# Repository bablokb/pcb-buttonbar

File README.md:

Project pcb-buttonbar
=====================

Overview
--------

This project contains the KiCAD files for a button-bar with
six buttons. Each button uses some additional hardware-components to
debounce the button:

The buttons are pulled up using R1. R2 and C1 serve as a lowpass-filter,
i.e. high frequency bouncing is filtered out. The final inverter, a
74HC14 is a Schmitt-Trigger type inverter. This inverter switches from
high to low at a different level than from low to high (hysteresis),
so this will convert the curve from the RC-filter to sharp edge.

Goodies
-------

The buttonbar supports buttons with four pins spaced 5.08mm x 5.08mm.
Note that normal buttons have spacings of 6.5mm x 4.5mm. 
In addition to the debounce-logic (bottom side of the pcb), there are optional
LEDs on the top.

The footprints for the top-side are 1206, suitable for hand-soldering.
The bottom-side uses 0603, ideal for automatic assembly.

Production Files
----------------

In the directory `production_files` you will find gerber-files, bom and cpl-file
suitable for JCLPCB. Migrating to a format suitable for your favorite
pcb-assembly service should be straightforward.

Test Program
------------

The directory `src` contains a simple test program. Without the debouncing
in hardware, you would have to pass an additional parameter to the
Button-constructor for debouncing in software.

License
-------

Shield: [![CC BY-SA 4.0][cc-by-sa-shield]][cc-by-sa]

This work is licensed under a
[Creative Commons Attribution-ShareAlike 4.0 International
License][cc-by-sa].

[![CC BY-SA 4.0][cc-by-sa-image]][cc-by-sa]

[cc-by-sa]: http://creativecommons.org/licenses/by-sa/4.0/
[cc-by-sa-image]: https://licensebuttons.net/l/by-sa/4.0/88x31.png
[cc-by-sa-shield]:
https://img.shields.io/badge/License-CC%20BY--SA%204.0-lightgrey.svg

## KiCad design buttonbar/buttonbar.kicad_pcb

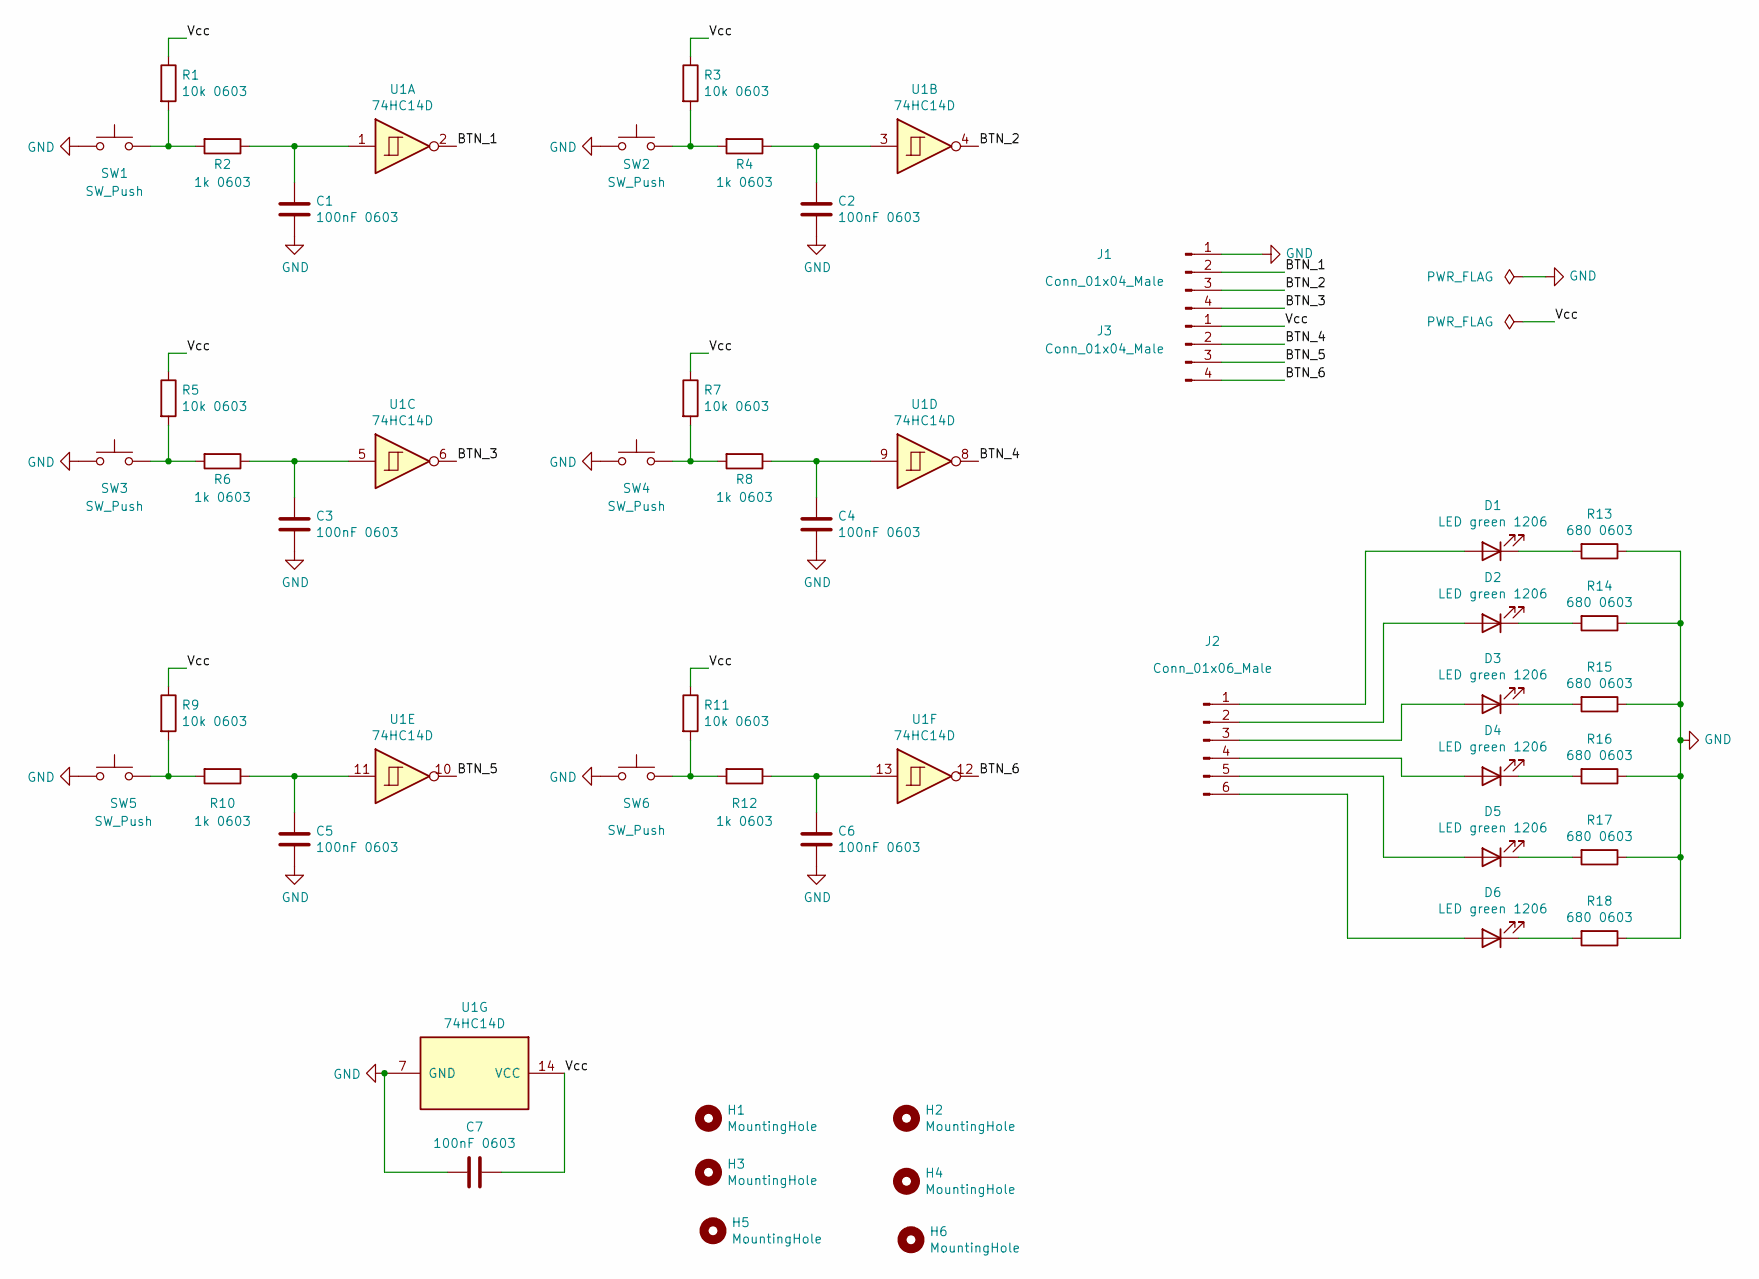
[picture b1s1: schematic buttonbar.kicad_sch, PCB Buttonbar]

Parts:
C1, C2, C3, C4, C5, C6, C7: 100nF 0603; C_0603_1608Metric; LCSC C14663
D1, D2, D3, D4, D5, D6: LED green 1206; LED_1206_3216Metric_Pad1.42x1.75mm_HandSolder
H1, H2, H3, H4, H5, H6: MountingHole; MountingHole_2.5mm
J1, J3: Conn_01x04_Male; PinHeader_1x04_P2.54mm_Vertical
J2: Conn_01x06_Male; PinHeader_1x06_P2.54mm_Vertical
R1, R3, R5, R7, R9, R11: 10k 0603; R_0603_1608Metric; LCSC C25804
R2, R4, R6, R8, R10, R12: 1k 0603; R_0603_1608Metric; LCSC C21190
R13, R14, R15, R16, R17, R18: 680 0603; R_0603_1608Metric; LCSC C23212
SW1, SW2, SW3, SW4, SW5, SW6: SW_Push; SW_PUSH_5.08mm
U1: 74HC14D; SOIC-14_3.9x8.7mm_P1.27mm; LCSC C5605

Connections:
/BTN_1: J1.2, U1.2
/BTN_2: J1.3, U1.4
/BTN_3: J1.4, U1.6
/BTN_4: J3.2, U1.8
/BTN_5: J3.3, U1.10
/BTN_6: J3.4, U1.12
/Vcc: C7.1, J3.1, R1.1, R3.1, R5.1, R7.1, R9.1, R11.1, U1.14 (VCC)
GND: C1.2, C2.2, C3.2, C4.2, C5.2, C6.2, C7.2, J1.1, R13.1, R14.1, R15.1, R16.1, R17.1, R18.1, SW1.1, SW2.1, SW3.1, SW4.1, SW5.1, SW6.1, U1.7 (GND)
unnamed: C1.1, R2.1, U1.1
unnamed: C2.1, R4.1, U1.3
unnamed: C3.1, R6.1, U1.5
unnamed: C4.1, R8.1, U1.9
unnamed: C5.1, R10.1, U1.11
unnamed: C6.1, R12.1, U1.13
unnamed: D1.1 (K), R13.2
unnamed: D1.2 (A), J2.1
unnamed: D2.1 (K), R14.2
unnamed: D2.2 (A), J2.2
unnamed: D3.1 (K), R15.2
unnamed: D3.2 (A), J2.3
unnamed: D4.1 (K), R16.2
unnamed: D4.2 (A), J2.4
unnamed: D5.1 (K), R17.2
unnamed: D5.2 (A), J2.5
unnamed: D6.1 (K), R18.2
unnamed: D6.2 (A), J2.6
unnamed: R1.2, R2.2, SW1.2
unnamed: R3.2, R4.2, SW2.2
unnamed: R5.2, R6.2, SW3.2
unnamed: R7.2, R8.2, SW4.2
unnamed: R9.2, R10.2, SW5.2
unnamed: R11.2, R12.2, SW6.2

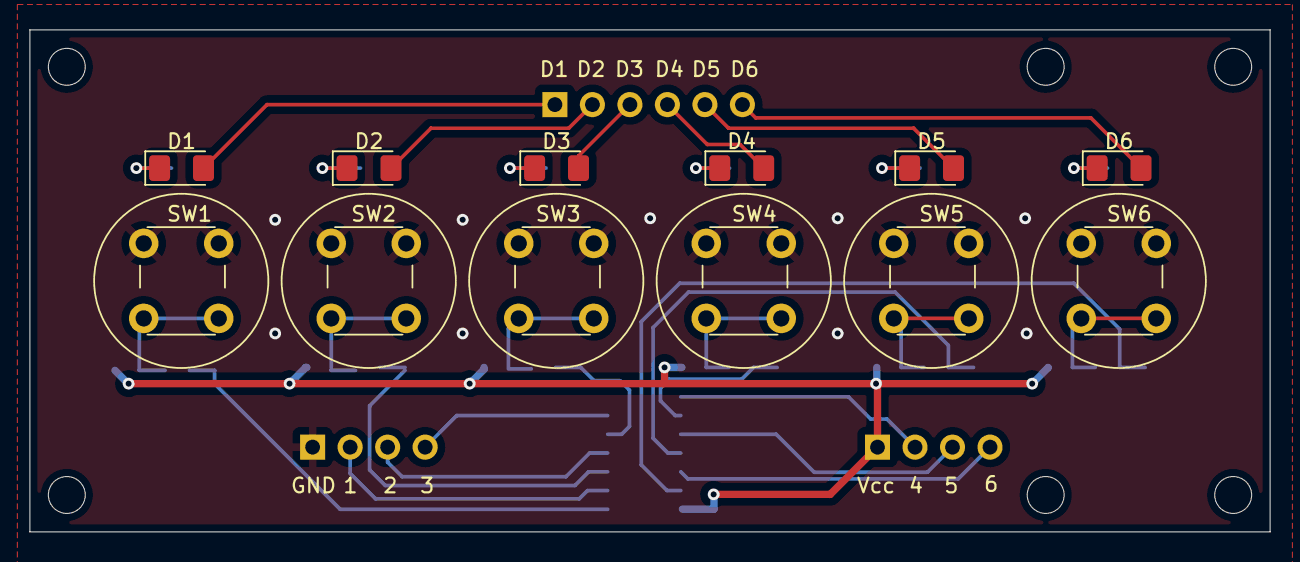
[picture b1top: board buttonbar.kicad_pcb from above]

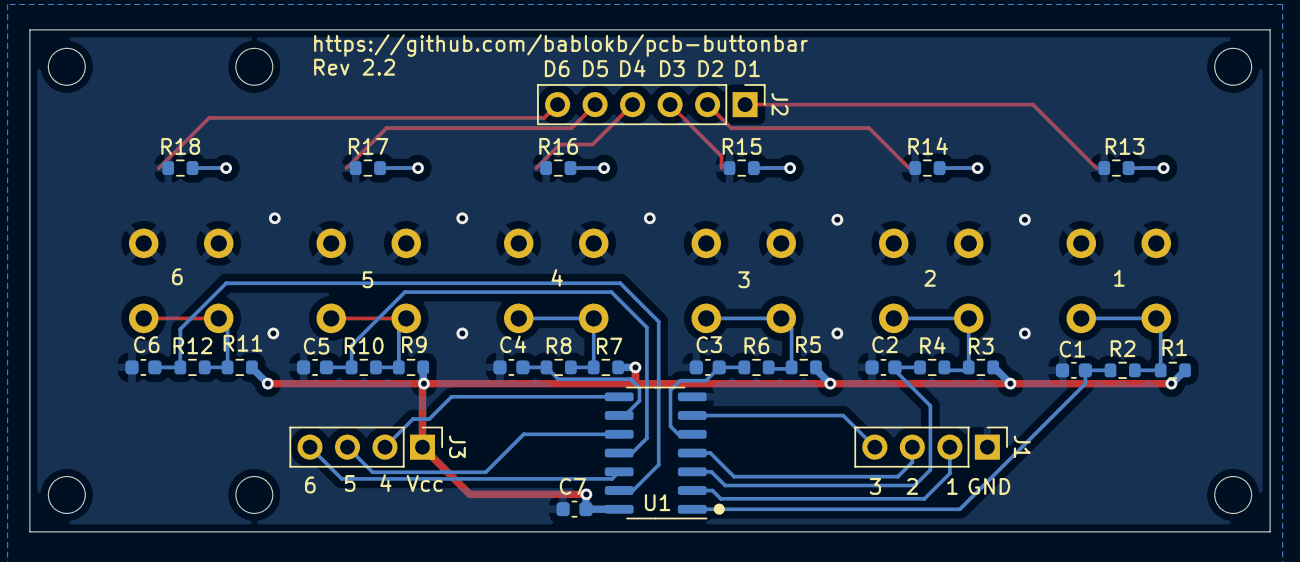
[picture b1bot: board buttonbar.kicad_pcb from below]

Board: 2 copper layers, 84.0 x 34.0 mm, 47 parts (29 on the bottom side), 32 nets.

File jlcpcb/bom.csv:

Comment,Designator,Footprint,LCSC
"100nF 0603","C1,C2,C3,C4,C5,C6,C7","Capacitor_SMD:C_0603_1608Metric","C14663"
"LED green 1206","D1,D2,D3,D4,D5,D6","LED_SMD:LED_1206_3216Metric_Pad1.42x1.75mm_HandSolder",""
"MountingHole","H1,H2,H3,H4","MountingHole:MountingHole_2.5mm",""
"Conn_01x08_Male","J1","Connector_PinHeader_2.54mm:PinHeader_1x08_P2.54mm_Vertical",""
"Conn_01x06_Male","J2","Connector_PinHeader_2.54mm:PinHeader_1x06_P2.54mm_Vertical",""
"10k 0603","R1,R3,R5,R7,R9,R11","Resistor_SMD:R_0603_1608Metric","C25804"
"680 1206","R13,R14,R15,R16,R17,R18","Resistor_SMD:R_1206_3216Metric_Pad1.30x1.75mm_HandSolder",""
"1k 0603","R2,R4,R6,R8,R10,R12","Resistor_SMD:R_0603_1608Metric","C21190"
"SW_Push","SW1,SW2,SW3,SW4,SW5,SW6","user:SW_PUSH-6.12mm",""
"74HC14D","U1","Package_SO:SOIC-14_3.9x8.7mm_P1.27mm","C5605"

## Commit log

2021-09-21 added generated files
2021-10-07 added content
2021-10-08 Rev 1.1: added labels (no functional change)
2021-10-30 link to images
2021-10-30 added section about license
2023-02-09 migrated to Kicad 6
2023-02-11 removed old jlcpcb-directory
2023-02-11 Rev 2.1
2023-02-11 added (directory) jlcpcb
2023-02-11 Rev 2.2 (in production)
2023-02-11 renamed 'jlcpcb' to 'production_files'
2023-02-11 minor changes
2023-02-11 minor updates for Rev 2.2
2023-02-21 changed comment
2025-03-31 added openscad model for spacer
2025-03-31 added *.stl list of ignored files
